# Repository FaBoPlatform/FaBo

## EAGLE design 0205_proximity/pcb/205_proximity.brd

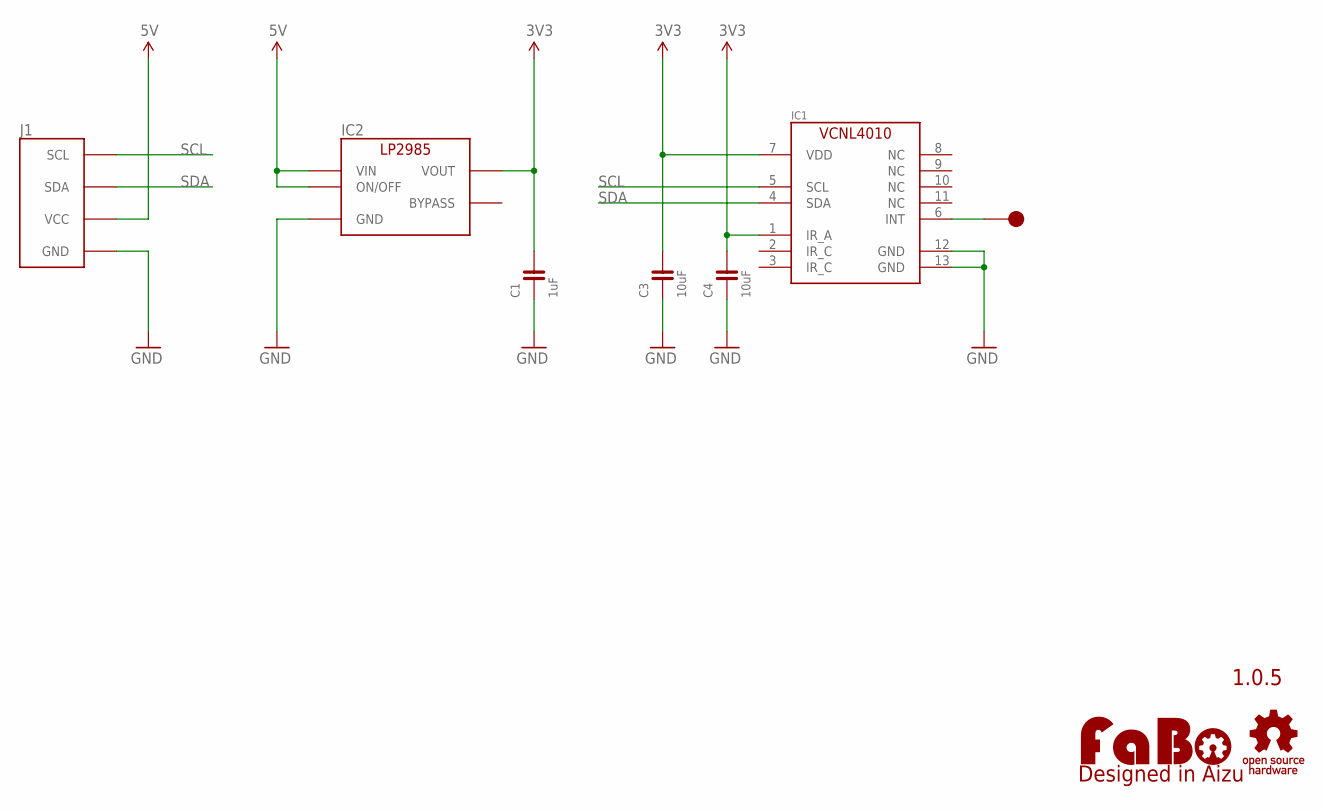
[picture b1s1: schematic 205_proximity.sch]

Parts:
C1: 1uF; 0603
C3, C4: 10uF; 0603
IC1: VCNL4010; VCNL4010-GS08
IC2: LP2985-33DBV; SOT-23-5
J1: FABO_BRICK_I2C
LOGO1: LOGO_FABO-M; LOGO_FABO_M
TP1: TP-15
U$2: LOGO_OSHW-M_BOTTOM; LOGO_OSHW_M_BOTTOM

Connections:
3V3: C1.2, C3.2, C4.2, IC1.1 (IR_A), IC1.7 (VDD), IC2.5 (VOUT)
5V: IC2.1 (VIN), IC2.3 (ON/OFF), J1.VCC
GND: C1.1, C3.1, C4.1, IC1.12 (GND), IC1.13 (GND), IC2.2 (GND), J1.GND
unnamed: IC1.6 (INT), TP1.1
SCL: IC1.5 (SCL), J1.SCL
SDA: IC1.4 (SDA), J1.SDA

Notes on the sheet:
1.0.5

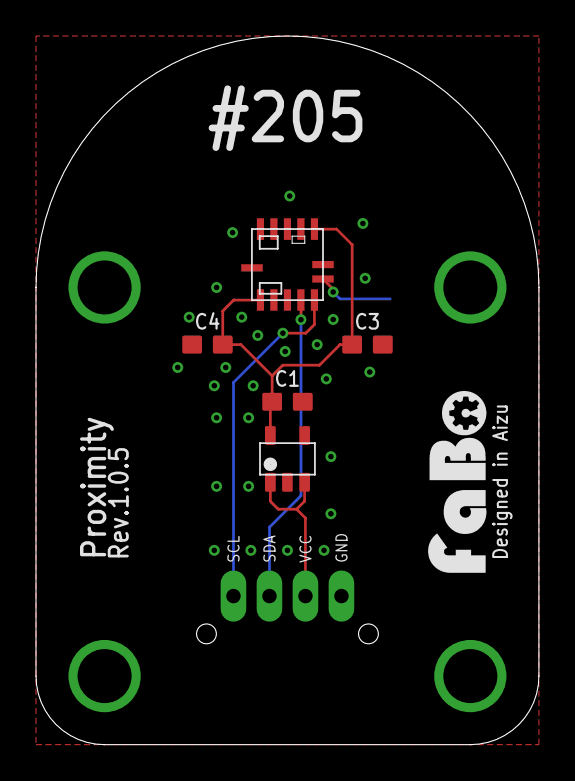
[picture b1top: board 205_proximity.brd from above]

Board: 2 copper layers, 27.9 x 39.4 mm, 9 parts (1 on the bottom side), 6 nets.

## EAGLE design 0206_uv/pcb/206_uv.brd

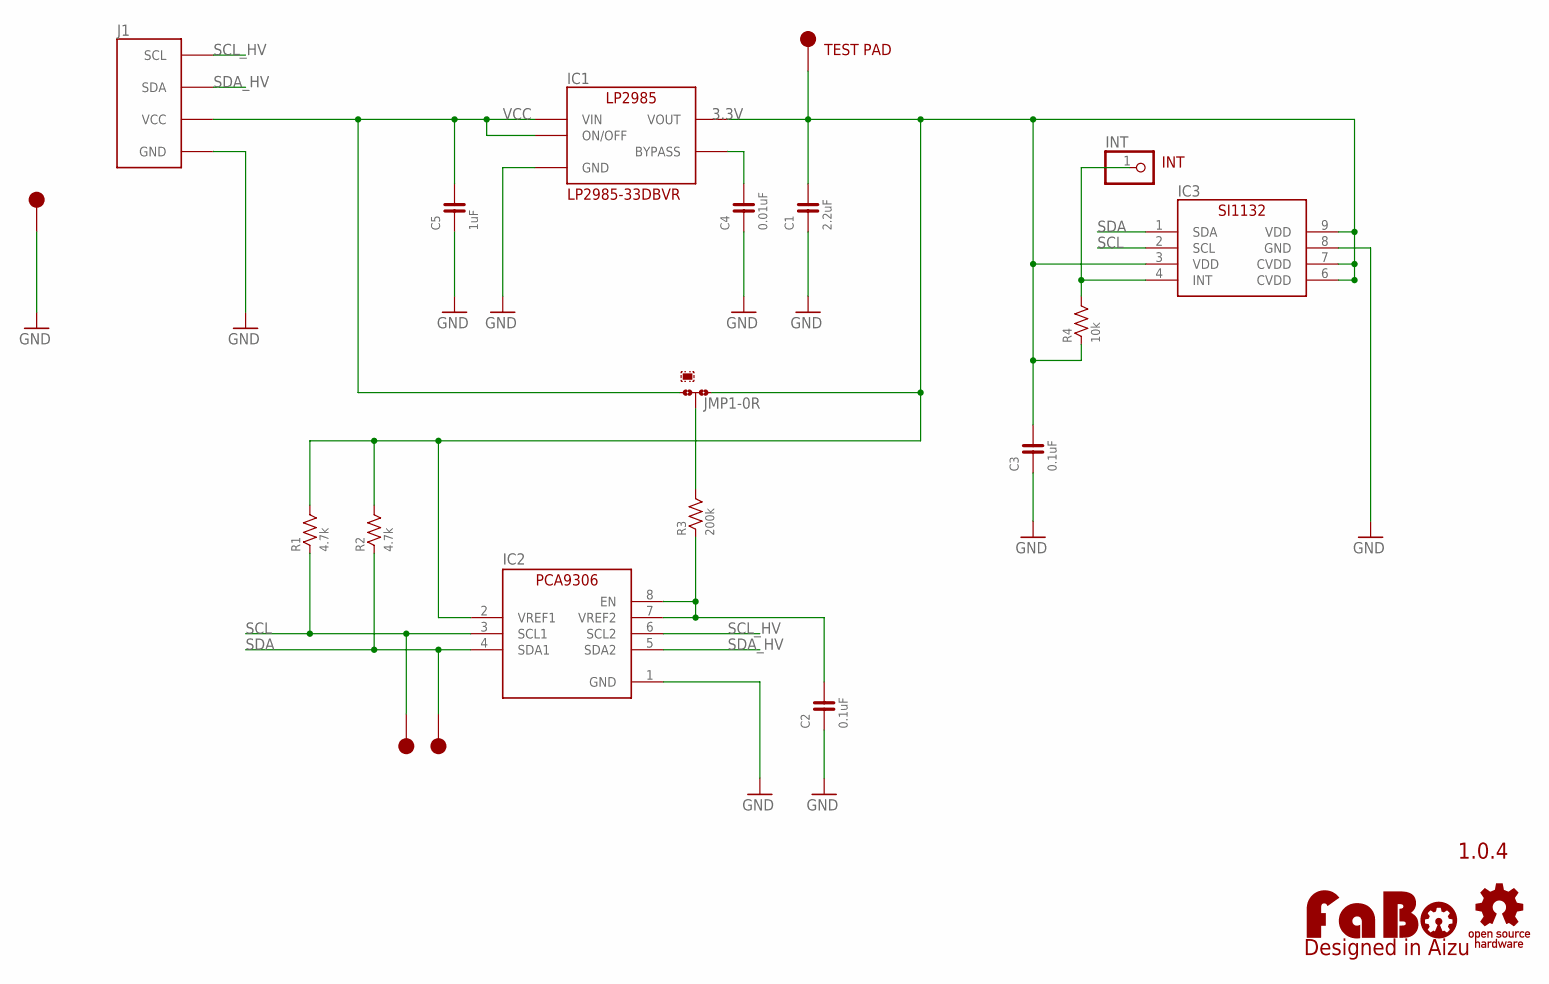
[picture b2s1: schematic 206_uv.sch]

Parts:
C1: 2.2uF; 0603
C2, C3: 0.1uF; 0603
C4: 0.01uF; 0603
C5: 1uF; 0603
IC1: LP2985-33DBV; SOT-23-5
IC2: PCA9306GM; XQFN8
IC3: SL-SI1132; SILICONLABS-SI1132
INT: PINHD-1X1; 1X01
J1: FABO_BRICK_I2C
JMP1: 0R-JUMPB; B0R-JMP
LOGO1: LOGO_FABO-M; LOGO_FABO_M
R1, R2: 4.7k; 0603
R3: 200k; 0603
R4: 10k; 0603
TP1, TP2, TP3, TP4: TP-15
U$3: LOGO_OSHW-M_BOTTOM; LOGO_OSHW_M_BOTTOM

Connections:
3.3V: C1.2, C3.2, IC1.5 (VOUT), IC2.2 (VREF1), IC3.3 (VDD), IC3.6 (CVDD), IC3.7 (CVDD), IC3.9 (VDD), JMP1.1, R1.2, R2.2, R4.1, TP4.1
GND: C1.1, C2.1, C3.1, C4.1, C5.1, IC1.2 (GND), IC2.1 (GND), IC3.8 (GND), J1.GND, TP3.1
unnamed: C2.2, IC2.7 (VREF2), IC2.8 (EN), R3.1
unnamed: C4.2, IC1.4 (BYPASS)
unnamed: JMP1.2, R3.2
unnamed: IC3.4 (INT), INT.1, R4.2
SCL: IC2.3 (SCL1), IC3.2 (SCL), R1.1, TP2.1
SCL_HV: IC2.6 (SCL2), J1.SCL
SDA: IC2.4 (SDA1), IC3.1 (SDA), R2.1, TP1.1
SDA_HV: IC2.5 (SDA2), J1.SDA
VCC: C5.2, IC1.1 (VIN), IC1.3 (ON/OFF), J1.VCC, JMP1.3

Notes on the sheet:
1.0.4
INT
TEST PAD
LP2985-33DBVR

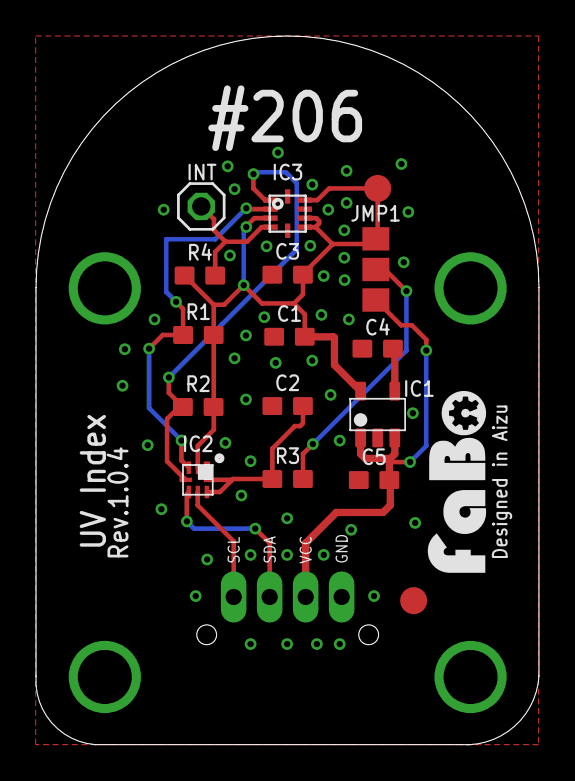
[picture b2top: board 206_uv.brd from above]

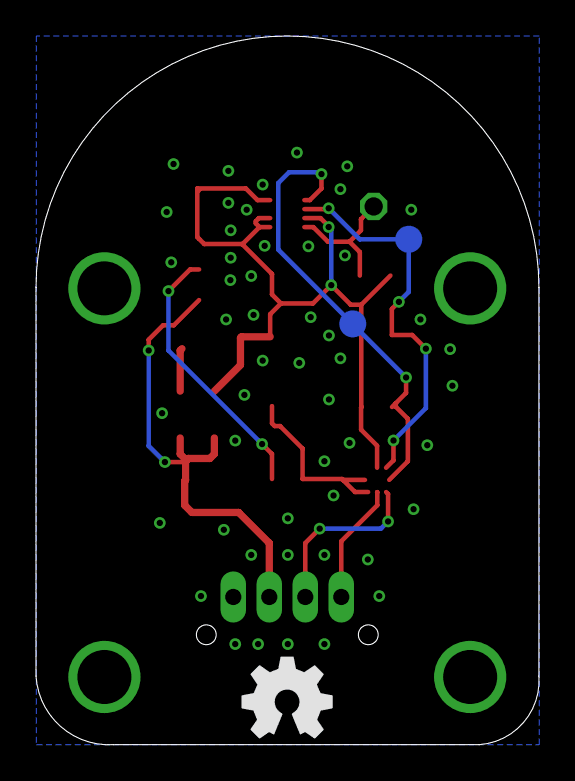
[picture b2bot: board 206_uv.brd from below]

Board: 2 copper layers, 27.9 x 39.4 mm, 22 parts (2 on the bottom side), 11 nets.

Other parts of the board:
U$4: FABO_BRICK_I2C_OUTTER

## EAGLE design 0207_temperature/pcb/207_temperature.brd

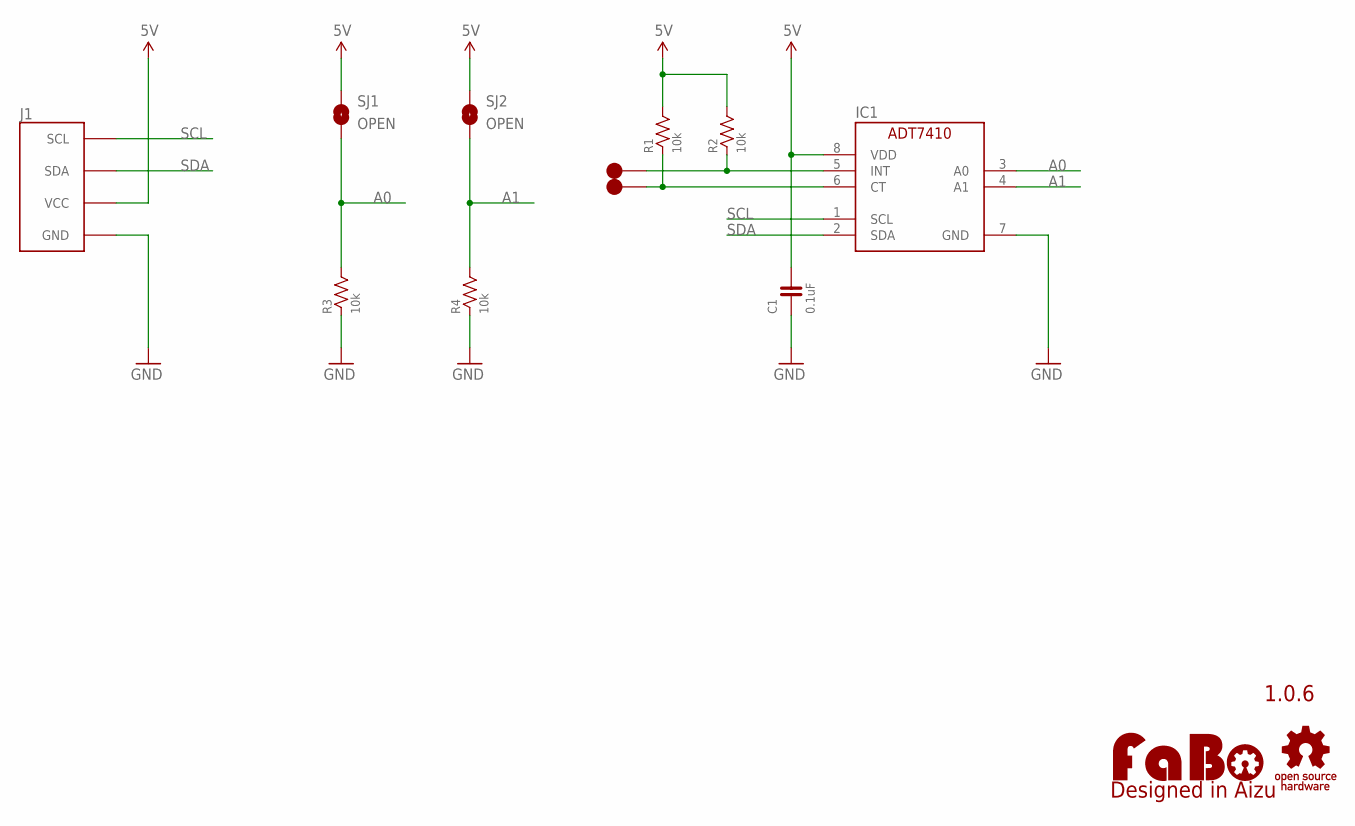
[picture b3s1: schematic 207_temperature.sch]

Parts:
C1: 0.1uF; 0603
IC1: AD-ADT7410; ANALOGDEVICES-ADT7410
J1: FABO_BRICK_I2C
LOGO1: LOGO_FABO-M; LOGO_FABO_M
R1, R2, R3, R4: 10k; 0603
SJ1, SJ2: OPEN; SMD-JUMPER-2-OPEN
TP1, TP2: TP-15
U$1: LOGO_OSHW-M_BOTTOM; LOGO_OSHW_M_BOTTOM

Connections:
5V: C1.2, IC1.8 (VDD), J1.VCC, R1.2, R2.2, SJ1.1, SJ2.1
A0: IC1.3 (A0), R3.2, SJ1.2
A1: IC1.4 (A1), R4.2, SJ2.2
GND: C1.1, IC1.7 (GND), J1.GND, R3.1, R4.1
unnamed: IC1.6 (CT), R1.1, TP2.1
unnamed: IC1.5 (INT), R2.1, TP1.1
SCL: IC1.1 (SCL), J1.SCL
SDA: IC1.2 (SDA), J1.SDA

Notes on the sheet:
1.0.6

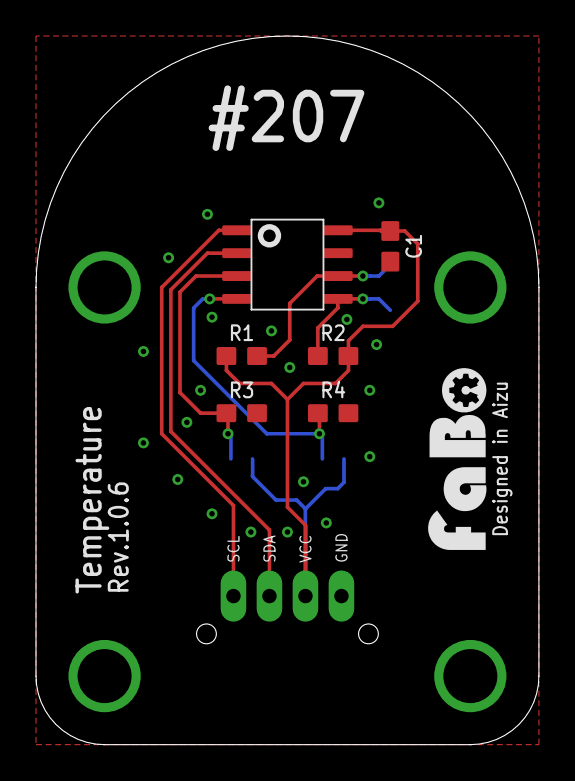
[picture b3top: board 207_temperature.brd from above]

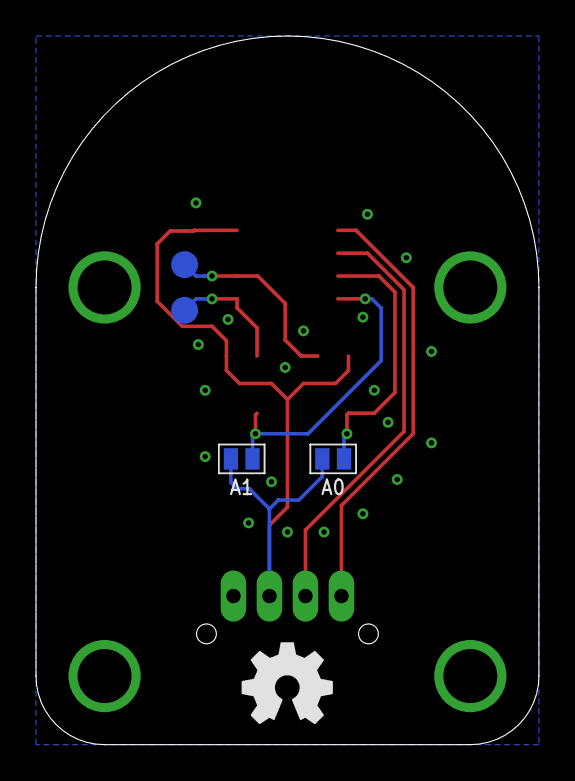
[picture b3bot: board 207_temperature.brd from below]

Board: 2 copper layers, 27.9 x 39.4 mm, 13 parts (4 on the bottom side), 8 nets.

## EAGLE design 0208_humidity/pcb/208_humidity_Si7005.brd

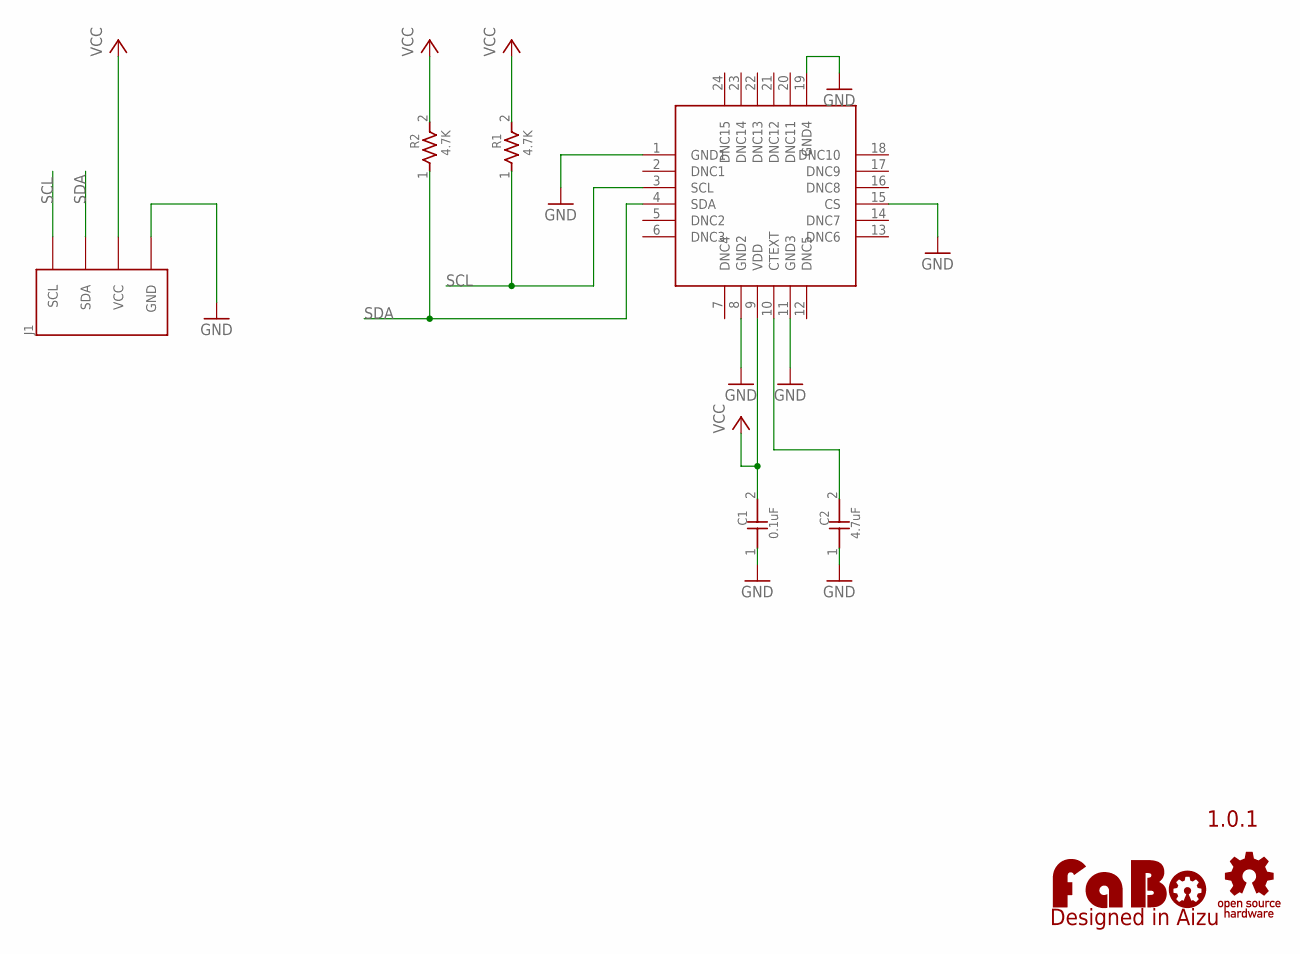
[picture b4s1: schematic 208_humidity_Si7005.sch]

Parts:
C1: 0.1uF; 0603
C2: 4.7uF; 0603
J1: BRICK_I2C
LOGO1: LOGO_FABO-M; LOGO_FABO_M
R1, R2: 4.7K; 0603
SI1: SILICONLAB-SI7005
U$2: LOGO_OSHW-M_BOTTOM; LOGO_OSHW_M_BOTTOM

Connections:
GND: C1.1, C2.1, J1.GND, SI1.1 (GND1), SI1.8 (GND2), SI1.11 (GND3), SI1.15 (CS), SI1.19 (GND4)
unnamed: C2.2, SI1.10 (CTEXT)
SCL: J1.SCL, R1.1, SI1.3 (SCL)
SDA: J1.SDA, R2.1, SI1.4 (SDA)
VCC: C1.2, J1.VCC, R1.2, R2.2, SI1.9 (VDD)

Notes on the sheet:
1.0.1

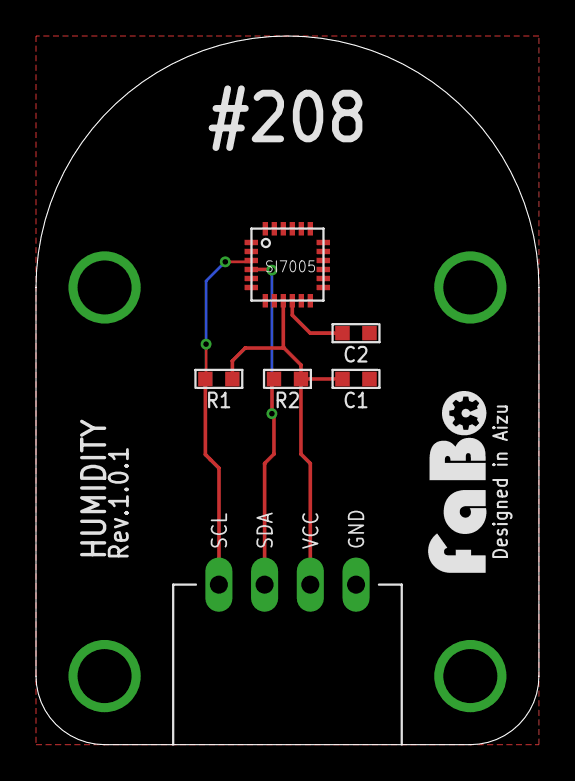
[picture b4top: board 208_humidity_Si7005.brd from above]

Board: 2 copper layers, 27.9 x 39.4 mm, 8 parts (0 on the bottom side), 5 nets.

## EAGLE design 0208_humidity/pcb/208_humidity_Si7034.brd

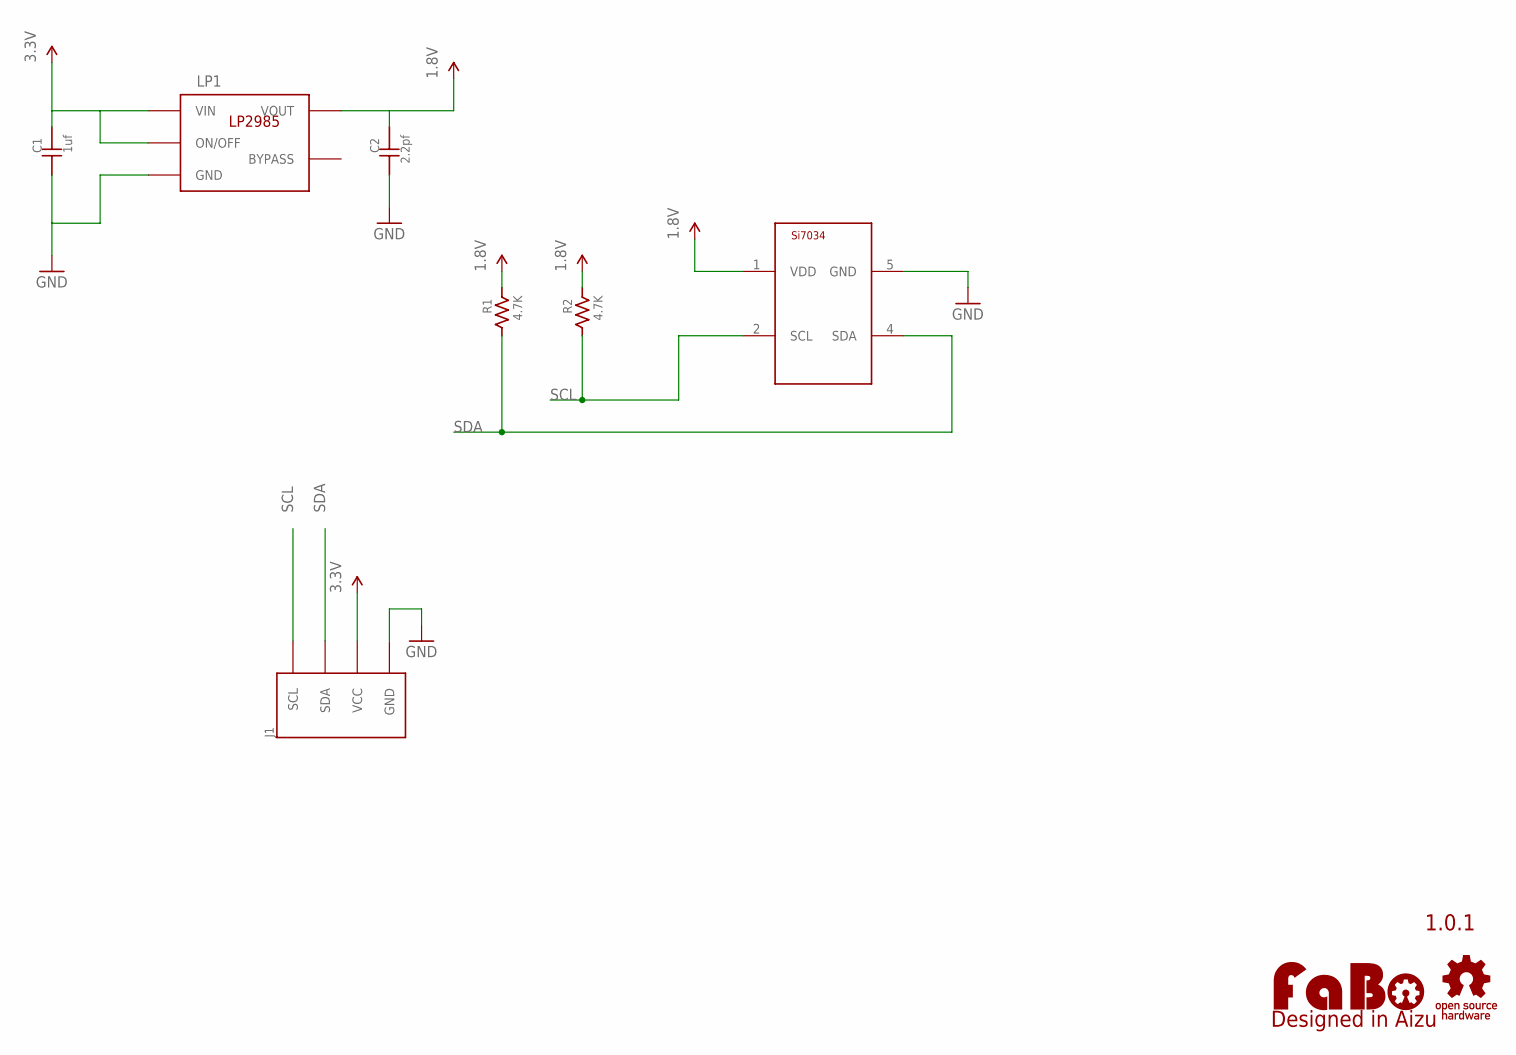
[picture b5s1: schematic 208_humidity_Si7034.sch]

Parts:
C1: 1uf; 0603
C2: 2.2pf; 0603
J1: BRICK_I2C
LOGO1: LOGO_FABO-M; LOGO_FABO_M
LP1: TI-LP2985-18DBVT; TI-LP2985
R1, R2: 4.7K; 0603
U$2: LOGO_OSHW-M_BOTTOM; LOGO_OSHW_M_BOTTOM
U$3: SILICONLABS-SI7034

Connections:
1.8V: C2.2, LP1.5 (VOUT), R1.2, R2.2, U$3.1 (VDD)
3.3V: C1.2, J1.VCC, LP1.1 (VIN), LP1.3 (ON/OFF)
GND: C1.1, C2.1, J1.GND, LP1.2 (GND), U$3.5 (GND)
SCL: J1.SCL, R2.1, U$3.2 (SCL)
SDA: J1.SDA, R1.1, U$3.4 (SDA)

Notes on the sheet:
1.0.1

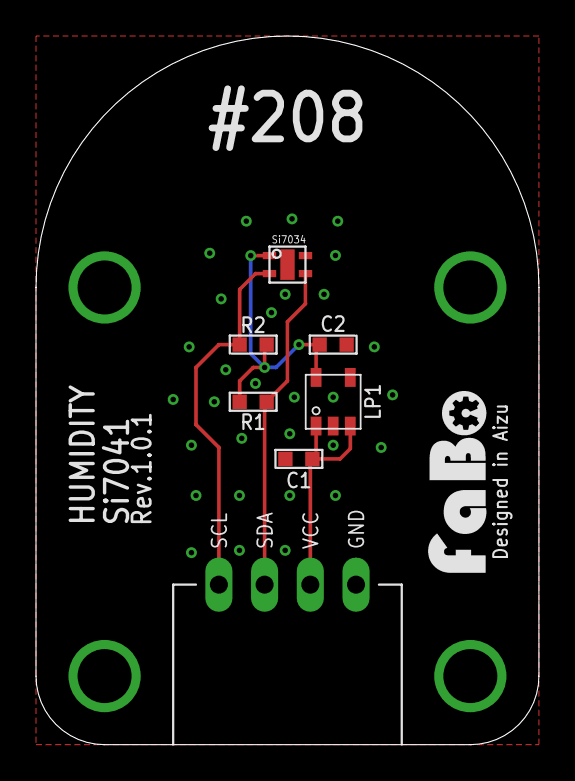
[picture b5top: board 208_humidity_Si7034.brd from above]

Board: 2 copper layers, 27.9 x 39.4 mm, 9 parts (0 on the bottom side), 5 nets.

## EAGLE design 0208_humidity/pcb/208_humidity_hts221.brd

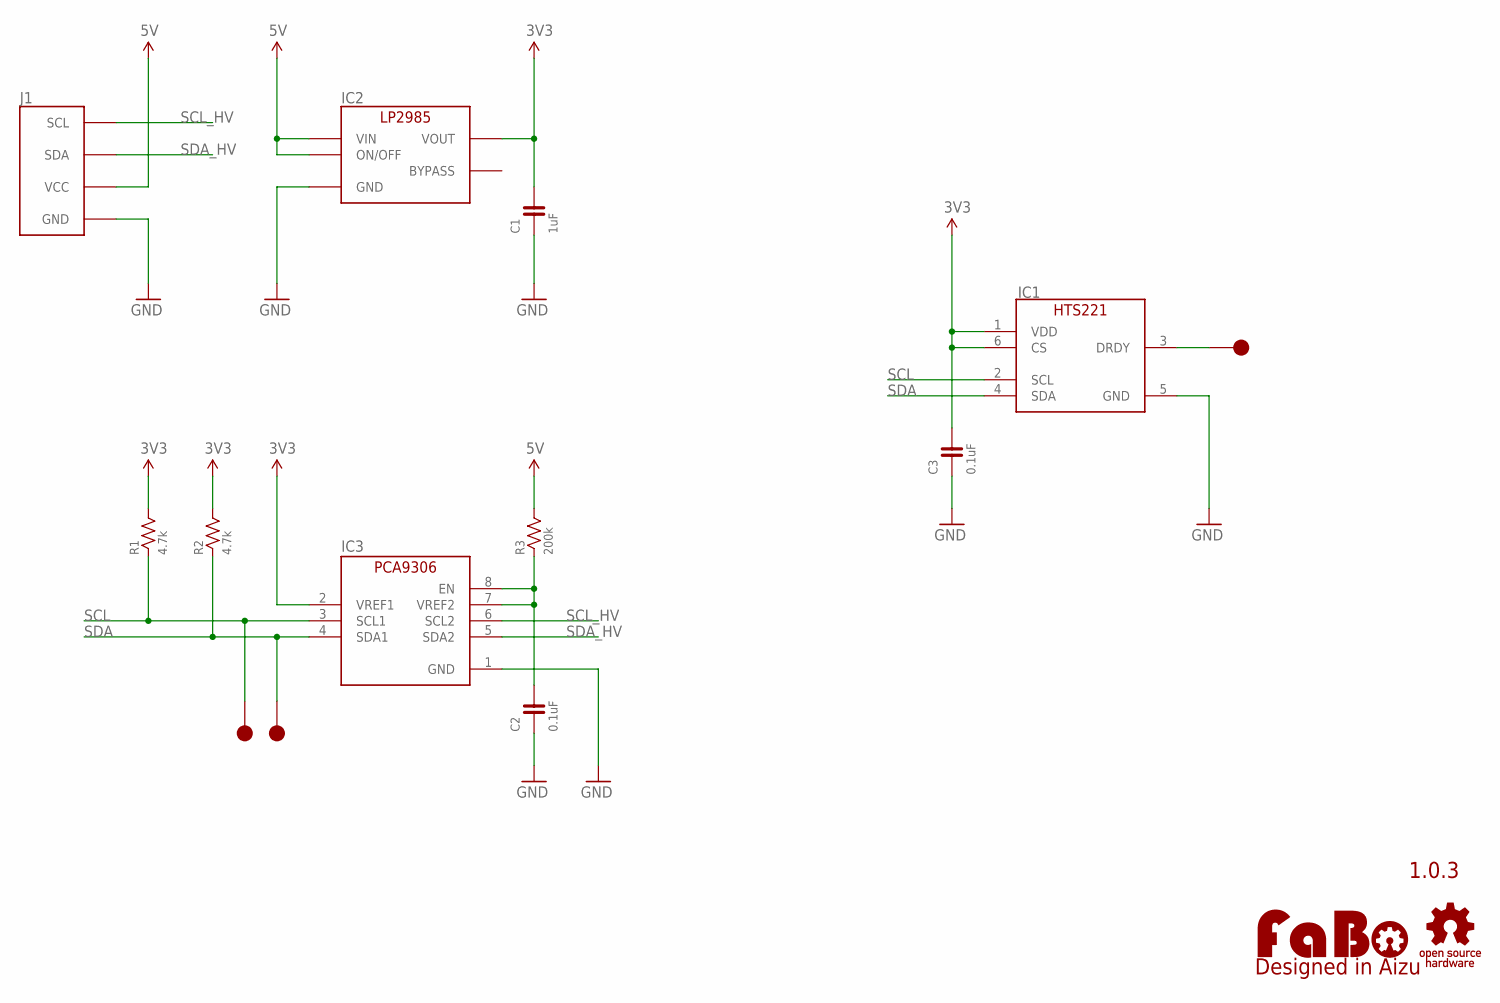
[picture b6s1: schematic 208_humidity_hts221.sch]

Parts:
C1: 1uF; 0603
C2, C3: 0.1uF; 0603
IC1: ST-HTS221
IC2: LP2985-33DBV; SOT-23-5
IC3: PCA9306GM; XQFN8
J1: FABO_BRICK_I2C
LOGO1: LOGO_FABO-M; LOGO_FABO_M
R1, R2: 4.7k; 0603
R3: 200k; 0603
TP1, TP2, TP3: TP-15
U$3: LOGO_OSHW-M_BOTTOM; LOGO_OSHW_M_BOTTOM

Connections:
3V3: C1.2, C3.2, IC1.1 (VDD), IC1.6 (CS), IC2.5 (VOUT), IC3.2 (VREF1), R1.2, R2.2
5V: IC2.1 (VIN), IC2.3 (ON/OFF), J1.VCC, R3.2
GND: C1.1, C2.1, C3.1, IC1.5 (GND), IC2.2 (GND), IC3.1 (GND), J1.GND
unnamed: C2.2, IC3.7 (VREF2), IC3.8 (EN), R3.1
unnamed: IC1.3 (DRDY), TP3.1
SCL: IC1.2 (SCL), IC3.3 (SCL1), R1.1, TP2.1
SCL_HV: IC3.6 (SCL2), J1.SCL
SDA: IC1.4 (SDA), IC3.4 (SDA1), R2.1, TP1.1
SDA_HV: IC3.5 (SDA2), J1.SDA

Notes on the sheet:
1.0.3

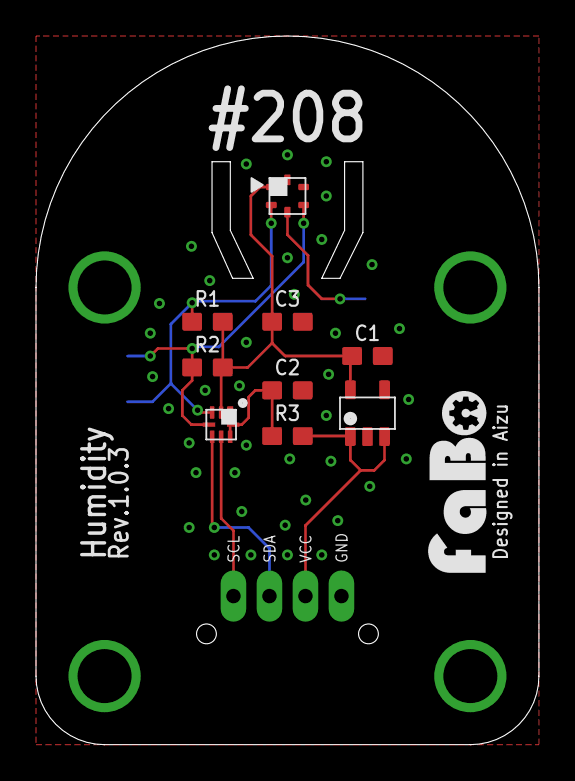
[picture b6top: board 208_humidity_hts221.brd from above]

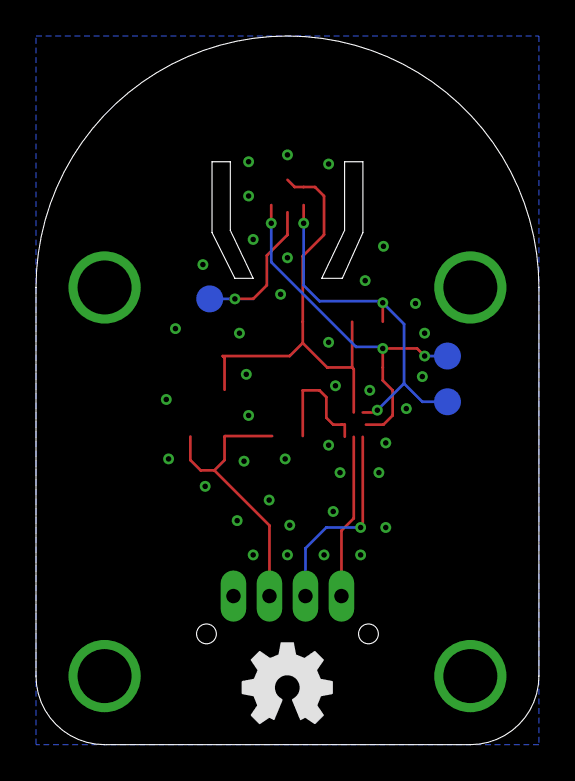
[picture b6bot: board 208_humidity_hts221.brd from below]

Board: 2 copper layers, 27.9 x 39.4 mm, 15 parts (3 on the bottom side), 9 nets.

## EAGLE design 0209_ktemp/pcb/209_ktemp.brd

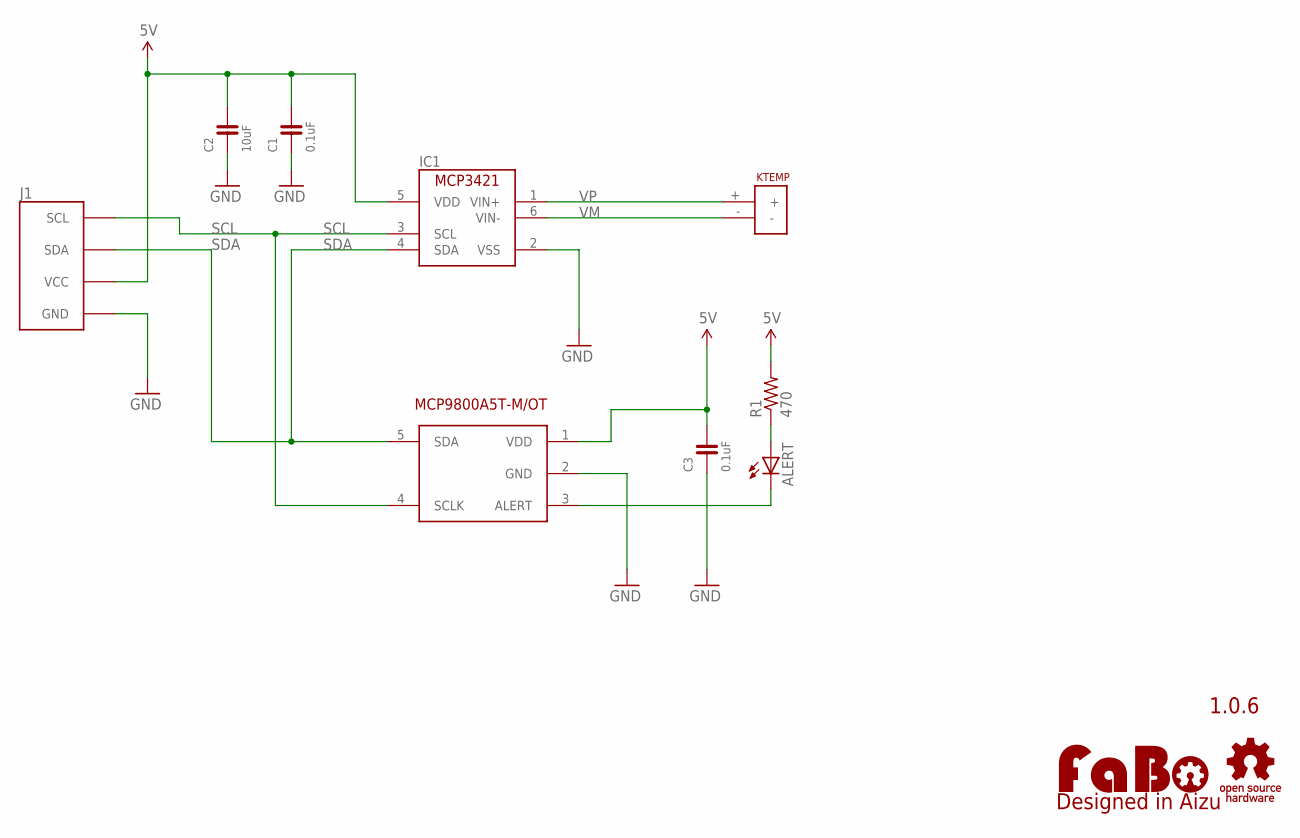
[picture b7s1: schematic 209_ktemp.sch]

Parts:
ALERT: LEDCHIP-LED0603; CHIP-LED0603
C1, C3: 0.1uF; 0603
C2: 10uF; 0603
IC1: MCP3421; SOT-23
J1: FABO_BRICK_I2CI2C_TEMP_LOG2; FABO_BRICK_I2C_LONG2
LOGO1: LOGO_FABO-M; LOGO_FABO_M
R1: 470; R0603
U$2: PCC-SMP-J
U$3: LOGO_OSHW-M_BOTTOM; LOGO_OSHW_M_BOTTOM
U$5: MCP9800_SOT-23; SOT23-5

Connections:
5V: C1.2, C2.2, C3.2, IC1.5 (VDD), J1.VCC, R1.2, U$5.1 (VDD)
GND: C1.1, C2.1, C3.1, IC1.2 (VSS), J1.GND, U$5.2 (GND)
unnamed: ALERT.A, R1.1
unnamed: ALERT.C, U$5.3 (ALERT)
SCL: IC1.3 (SCL), J1.SCL, U$5.4 (SCLK)
SDA: IC1.4 (SDA), J1.SDA, U$5.5 (SDA)
VM: IC1.6 (VIN-), U$2.-
VP: IC1.1 (VIN+), U$2.+

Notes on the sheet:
1.0.6

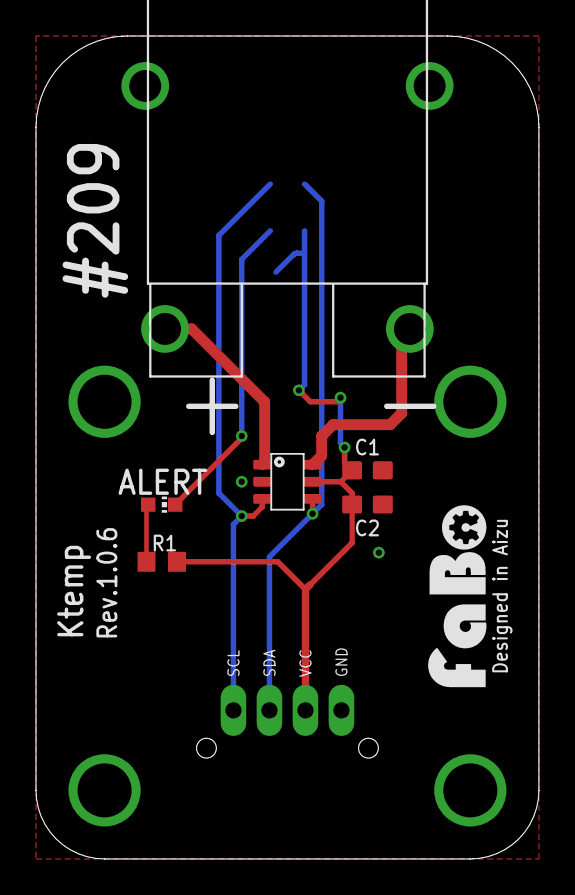
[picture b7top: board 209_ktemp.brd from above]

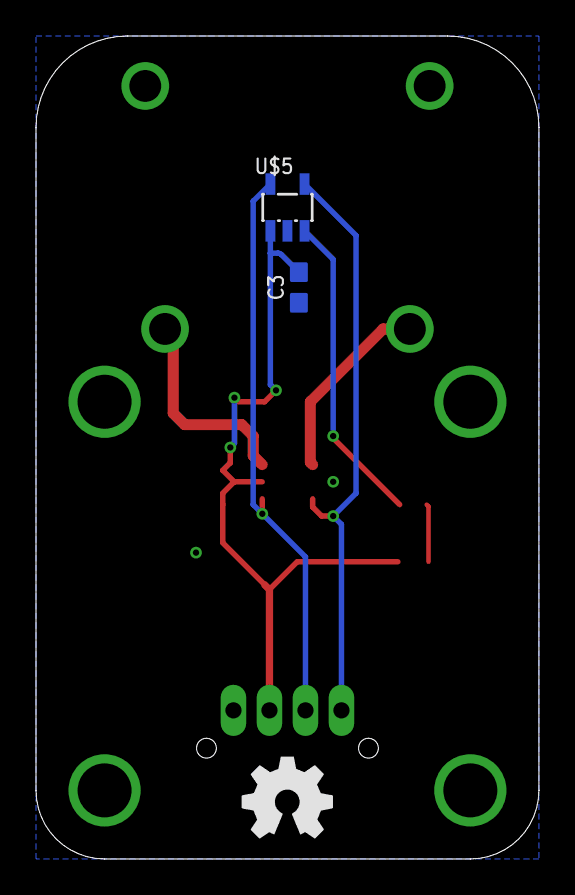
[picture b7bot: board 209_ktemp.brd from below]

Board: 2 copper layers, 27.9 x 45.7 mm, 11 parts (2 on the bottom side), 8 nets.

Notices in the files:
parts and their libraries:
FaBo-etc: Released under the Creative Commons Attribution-ShareAlike 4.0 License
https://creativecommons.org/licenses/by-sa/4.0
FaBo-etc: Released under the Creative Commons
